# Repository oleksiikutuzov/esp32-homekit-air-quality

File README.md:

# ESP32 HomeKit Air Quality Sensor
Native Apple HomeKit via ESP32 for the IKEA VINDRIKTNING PM2.5 Air Quality sensor + MH-Z19B CO2 Sensor

The modification doesn't interfere with the VINDRIKTNING device itself. It just reads out data and passes it to HomeKit using ESP32.

This Firmware is a Frankenstein Monster built of some other IKEA VINDRIKTNING projects from kasik96, Hypfer and ESP32 HomeKit implementation from HomeSpan.

_As usual, don't expect any warranties. I am just a hobbyist, not a professional. It works for me, but you take your own risk using it. I am not liable for any damage to your devices._

I also added the MH-Z19B CO2 Sensor, which fits into the second enclosure along with a custom PCB, which can be glued (taped) on top of the VINDRIKTNING device. It follows the existing design and should look nice (I hope). It also has an LED to show the current CO2 level.

## Prerequisites

- ESP-32-WROOM with project PCB
- MH-Z19B CO2 sensor
- 1 NeoPixel LED
- Some short cables
- A soldering iron
- A long PH0 Screwdriver
- Some more components (check the [BOM](https://github.com/oleksiikutuzov/esp32-homekit-air-quality/blob/main/hardware/BOM.txt))

Everything we need from the IKEA sensor is accessible via easy-to-solder test points or microcontroller pins.

## Hardware
### VINDRIKTNING

To reach the original PCB from IKEA, we need to unscrew the four visible screws in the back of the enclosure.

As you can see in this image, you'll need to solder wires to GND (black), 5V (red), and the Testpoint that is connected to the TX of the
Particle Sensor (lighter green). Additionally, you need to solder the cable to one of the pins of the microcontroller (darker green) to be able to read the values from the built-in light sensor. On my PCB I am using a JST-GH (1.25 mm) connector to connect all the wires from VINDRIKTNING. Make sure the cables from IKEA PCB have enough cross-section to carry the current because generic Chinese JST-GH connectors' cables are too thin.

Solder the custom PCB, install the MH-Z19B CO2 sensor, connect the VINDRIKTNING board and NeoPixel LED via JST connectors and you are done.

### Sensor
The PCB has pads for 1.25 mm keyless 3-pin and 4-pin JST connectors, the lid has 4 mm holes for M3 threaded inserts and holes for small screws to fix the plate on which NeoPixel is mounted.

## Software

Here you can see, which pins are used and pre-defined in the firmware:
```c++
*               ╔═════════════════════════════╗
*               ║┌─┬─┐  ┌──┐  ┌─┐             ║
*               ║│ | └──┘  └──┘ |             ║
*               ║│ |            |             ║
*               ╠═════════════════════════════╣
*           +++ ║GND                       GND║ +++
*           +++ ║3.3V                     IO23║ USED_FOR_NOTHING
*               ║                         IO22║
*               ║IO36                      IO1║ TX
*               ║IO39                      IO3║ RX
*               ║IO34                     IO21║
*               ║IO35                         ║ NC
*               ║IO32                     IO19║ MHZ TX
*               ║IO33                     IO18║ MHZ RX
*  LIGHT_SENSOR ║IO25                      IO5║
*       LED_RED ║IO26                     IO17║
*               ║IO27                     IO16║ NEOPIXEL
*  VINDRIKTNING ║IO14                      IO4║
*               ║IO12                      IO0║ BUTTONS
*               ╚═════════════════════════════╝
```

The firmware can be built and flashed using the Arduino IDE.

For this, you will need to add ESP32 support to it.

Furthermore, you will also need to install the following libraries using the Library Manager:

* Adafruit NeoPixel
* HomeSpan
* EspSoftwareSerial

And some libraries manually:

1. Go to this GitHub repo and download it as a ZIP - [AsyncElegantOTA](https://github.com/ayushsharma82/AsyncElegantOTA)
2. In Arduino IDE select "Sketch" -> "Include Library" and "Add .ZIP Library..." and select downloaded ZIP
3. Do previous steps to the following libraries:
   * [ESPAsyncWebServer](https://github.com/me-no-dev/ESPAsyncWebServer)
   * [AsyncTCP](https://github.com/me-no-dev/AsyncTCP)
   * [ErriezMHZ19B](https://github.com/Erriez/ErriezMHZ19B)
4. Download and open this repository in Arduino IDE (or VSCode with Arduino extension)
5. Set the upload speed to 115200
6. Build, flash, and you're done

Instead of Arduino IDE OTA, the web server update was implemented. You can flash binary at `http://[DEVICE IP]/update`.
There is a reboot link. Opening `http://[DEVICE IP]/reboot` will force the device to reboot.

The device can also be controlled by the button on the backside. More on [HomeSpan docs](https://github.com/HomeSpan/HomeSpan/blob/master/docs/UserGuide.md)

A list of settings variables is in the sketch. You can adjust the values up to your needs.

## Connect to HomeKit

1. Plug your Air Quality sensor to power (ESP32 is powered through VINDRIKTNING).
2. Press the button on the backside until the LED starts blinking rapidly and release it. Now it is in the configuration mode (More on [HomeSpan docs](https://github.com/HomeSpan/HomeSpan/blob/master/docs/UserGuide.md)). Press it two more times until the LED starts blinking 3 times in a row. This means mode 3 is chosen. Hold the button for 3-4 seconds once again and the WiFi AP will be started.
3. Go to WiFi settings on your iPhone/iPad and connect to the "HomeSpan-Setup" WiFi network, password `homespan`.
4. You will choose your WiFi network and set the setup code for the accessory.
5. Go to your Home app and select "Add Accessory"
6. Select "More Options" and you should see your Air Quality Sensor there.

## Prometheus metrics

The firmware creates a simple HTTP server to share the metrics to the Prometheus host server. The update interval is 10 seconds, the same as for the HomeKit data. Is available at the `http://DEVICE_IP/metrics` default port is `80`.

Installation guides for Raspberry Pi 4: [Grafana](https://pimylifeup.com/raspberry-pi-grafana/), [Prometheus](https://pimylifeup.com/raspberry-pi-prometheus/).

To add metrics to your Prometheus config:

1. Stop the Prometheus service:
```
sudo systemctl stop prometheus
```
2. Edit your config:
```
nano /home/pi/prometheus/prometheus.yml
```
Paste the following to the end of the config (Keep in mind indentation):
```
- job_name: "air_sensor"
    scrape_interval: 30s
    honor_labels: true
    static_configs:
    - targets: ['DEVICE_IP:80']
```
*Scrape interval determines, how often the server will check the device for metrics updates*

3. Start the Prometheus service again:
```
sudo systemctl start prometheus
```

## References and sources

- @kasik96 for HomeKit ESP8266 VINDRIKTNING custom firmware [GitHub link](https://github.com/kasik96/esp8266-vindriktning-particle-sensor-homekit)
- @Hypfer for MQTT ESP8266 VINDRIKTNING custom firmware [GitHub link](https://github.com/Hypfer/esp8266-vindriktning-particle-sensor)
- @HomeSpan for ESP32 HomeKit firmware [GitHub link](https://github.com/HomeSpan/HomeSpan)
- @Erriez for MH-Z19B CO2 sensor library [GitHub link](https://github.com/Erriez/ErriezMHZ19B)
- [@haxfleisch](https://twitter.com/haxfleisch) for their teardown of the device.

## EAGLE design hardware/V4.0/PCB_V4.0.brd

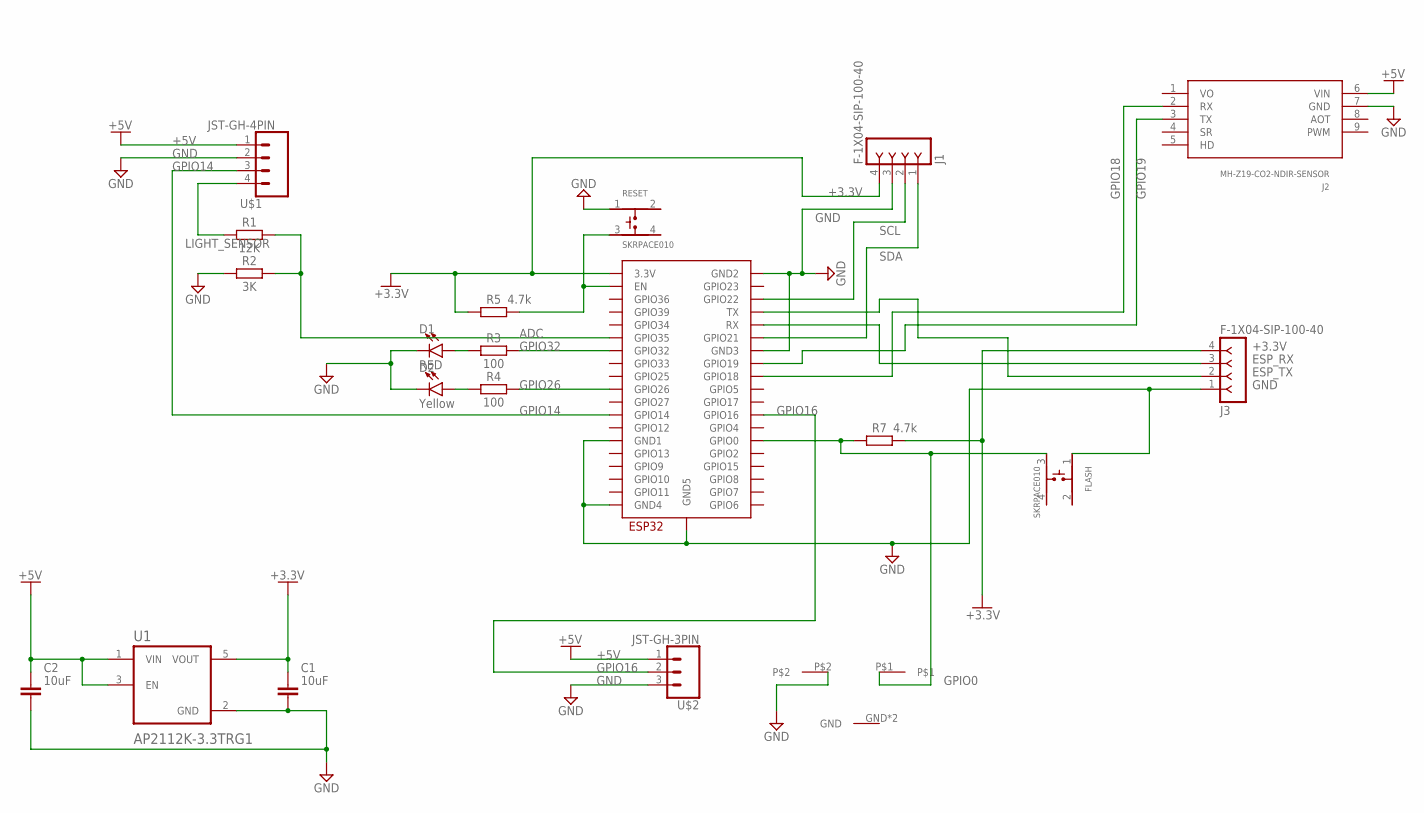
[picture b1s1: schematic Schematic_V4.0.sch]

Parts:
C1, C2: 10uF; CAPC1608X85
D1: RED; LED-0603
D2: Yellow; LED-0603
FLASH: SKRPACE010; SW_SKRPACE010
J1, J3: F-1X04-SIP-100-40; SIP-100-04-40
J2: MH-Z19-CO2-NDIR-SENSOR; MH-Z19
R1: 12K; RESC1608X60
R2: 3K; RESC1608X60
R3, R4: 100; RESC1608X60
R5, R7: 4.7k; RESC1608X60
RESET: SKRPACE010; SW_SKRPACE010
U1: AP2112K-3.3TRG1; SOT95P285X140-5N
U$1: JST-GH-4PIN
U$2: JST-GH-3PIN
U$3: ESP32-WROOM
U$4: MOMENTARY-SWITCH; SWITCH-MOMENTARY

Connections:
+3.3V: C1.1, J1.4, J3.4, R5.1, R7.2, U1.5 (VOUT), U$3.3V3 (3.3V)
+5V: C2.1, J2.6 (VIN), U1.1 (VIN), U1.3 (EN), U$1.1, U$2.1
ADC: R1.2, R2.2, U$3.IO35 (GPIO35)
ESP_RX: J3.3, U$3.RX
ESP_TX: J3.2, U$3.TX
GND: C1.2, C2.2, D1.C, D2.C, FLASH.1, J1.3, J2.7 (GND), J3.1, R2.1, RESET.1, U1.2 (GND), U$1.2, U$2.3, U$3.GND1, U$3.GND2, U$3.GND3, U$3.GND4, U$3.GND5, U$4.P$2
GPIO0: FLASH.3, R7.1, U$3.IO0 (GPIO0), U$4.P$1
GPIO14: U$1.3, U$3.IO14 (GPIO14)
GPIO16: U$2.2, U$3.IO16 (GPIO16)
GPIO18: J2.2 (RX), U$3.IO18 (GPIO18)
GPIO19: J2.3 (TX), U$3.IO19 (GPIO19)
GPIO26: R4.2, U$3.IO26 (GPIO26)
GPIO32: R3.2, U$3.IO32 (GPIO32)
LIGHT_SENSOR: R1.1, U$1.4
unnamed: D1.A, R3.1
unnamed: D2.A, R4.1
RESET: R5.2, RESET.3, U$3.EN
SCL: J1.2, U$3.IO22 (GPIO22)
SDA: J1.1, U$3.IO21 (GPIO21)
VO: J2.1 (VO)

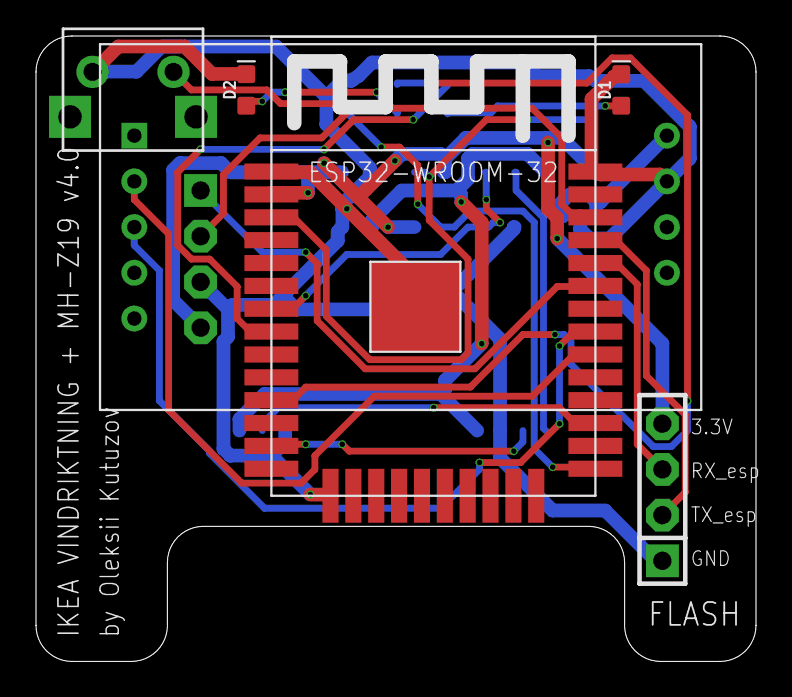
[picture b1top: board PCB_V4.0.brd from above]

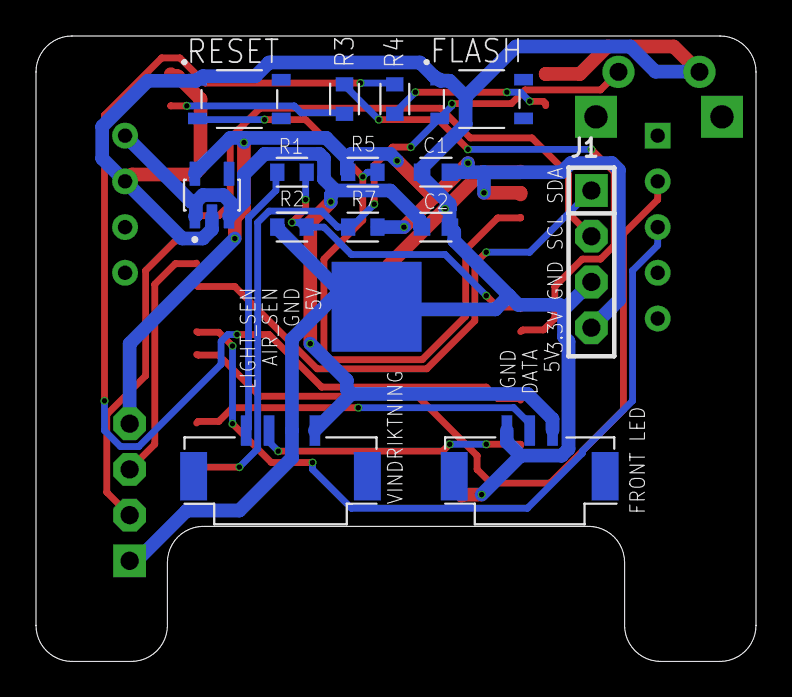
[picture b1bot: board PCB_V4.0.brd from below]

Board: 2 copper layers, 40.0 x 34.7 mm, 20 parts (14 on the bottom side), 19 nets.

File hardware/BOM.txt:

Part  Value                  Device                   Package          Description                                                                 
C1    10uF                   C_CHIP-0603(1608-METRIC) CAPC1608X85      Capacitor - Generic                                                         
C2    10uF                   C_CHIP-0603(1608-METRIC) CAPC1608X85      Capacitor - Generic                                                         
D2    RED                    LED-RED0603              LED-0603         Red SMD LED                                                                 
FLASH SKRPACE010             SKRPACE010               SW_SKRPACE010    Switch Tactile N.O. SPST Button J-Bend 0.05A 16VDC 2.55N SMD Automotive T/R 
J2    MH-Z19-CO2-NDIR-SENSOR MH-Z19-CO2-NDIR-SENSOR   MH-Z19           MH-Z19 - CO2 NDIR SENSOR                                                    
J3    F-1X04-SIP-100-40      F-1X04-SIP-100-40        SIP-100-04-40    FEMALE HEADER                                                               
R1    12K                    R_CHIP-0603(1608-METRIC) RESC1608X60      Resistor Fixed - Generic                                                    
R2    3K                     R_CHIP-0603(1608-METRIC) RESC1608X60      Resistor Fixed - Generic                                                    
R3    100                    R_CHIP-0603(1608-METRIC) RESC1608X60      Resistor Fixed - Generic                                                    
R4    100                    R_CHIP-0603(1608-METRIC) RESC1608X60      Resistor Fixed - Generic                                                    
R5    4.7k                   R_CHIP-0603(1608-METRIC) RESC1608X60      Resistor Fixed - Generic                                                    
R7    4.7k                   R_CHIP-0603(1608-METRIC) RESC1608X60      Resistor Fixed - Generic                                                    
RESET SKRPACE010             SKRPACE010               SW_SKRPACE010    https://a.aliexpress.com/_AWwm9c
U$1   JST-GH-4PIN            JST-GH-4PIN              JST-GH-4PIN      https://a.aliexpress.com/_9IWSRs                                                                           
U$2   JST-GH-3PIN            JST-GH-3PIN              JST-GH-3PIN      https://a.aliexpress.com/_9IWSRs                                                                           
U$3   ESP32-WROOM            ESP32-WROOM              ESP32-WROOM                                                                                 
U$4   MOMENTARY-SWITCH       MOMENTARY-SWITCH         SWITCH-MOMENTARY https://a.aliexpress.com/_AcqTm9 (6x6x6 mm)                                                                            
U1    AP2112K-3.3TRG1        AP2112K-3.3TRG1          SOT95P285X140-5N AP2112 Series 0.6 A 3.3 V Fixed Output SMT LDO Linear Regulator - SOT23-5

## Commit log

2022-02-10 Upload example code
2022-02-10 Adjust characteristics
2022-02-10 Remove comments
2022-02-10 Add support for MH-Z19B
2022-02-10 Move warming up to separate process
2022-02-10 Add initial animation
2022-02-11 Add color change on warm up and according to co2 level
2022-02-11 Add reset peak value
2022-02-11 Add VSCode config
2022-02-11 Add Air quality measurements
2022-02-11 Add autocalibration option
2022-02-11 Add metrics server
2022-02-11 Add uptime and heap metric
2022-02-11 Add brightness control
2022-02-13 Small adjustments to metrics server
2022-02-13 Set auto AP on startup
2022-02-13 Change default vo2 value to 400
2022-02-13 Adjust Accessories names
2022-02-13 Change interval to 10 seconds
2022-02-13 Set default value to exclude metrics during warmup
2022-04-26 Change server, add OTA
2022-04-26 Add timeout for the built in led
2022-05-05 Remove unneeded pin definitions
2022-05-05 Set number of connections to default value
2022-05-06 Set button pin to 0, disable auto AP
2022-05-06 Edit build config
2022-05-06 Remove most of libraries
2022-05-06 Add libraries
2022-05-06 Add more libraries
2022-05-06 Fix sketch name
2022-05-06 Edit libraries
2022-05-06 Add library
2022-05-06 Fix library name
2022-05-06 Add Smoothed library
2022-05-06 Add build parameters
2022-05-06 Change smoothing to library
2022-05-06 Update services
2022-05-06 Remove DEV_Identify.h
2022-05-06 Update config file
2022-05-06 Add hardware files
2022-05-06 Add pictures
2022-05-06 Small fixes
2022-05-07 Update config
2022-05-07 Rename folder
2022-05-07 Add submodules
2022-05-07 Remove submodules
2022-05-07 Remove .gitmodules
2022-05-07 Edit config files
2022-05-17 Small adjustments to config
2022-05-17 Adjust pin scheme
2022-05-17 Update Firmware Revision
2022-05-26 Change header files to .hpp
2022-05-26 Change includes to .hpp
2022-06-08 Update VSCode settings
2022-06-09 Apply some filtering to Air Quality Sensor data
2022-08-02 Change from AsyncWebServer to WebServer and misc
2022-08-02 Update VSCode config
2022-08-09 Minor fixes
2022-08-27 Add temperature and humidity, test brightness
2022-08-30 Add offset to temperature and humidity values
2022-08-30 Reorder hardware, upload new hardware revision
2022-08-30 Apply smoothing to sensor data
2022-08-30 Add sensor values to prometheus metrics
2022-08-30 Warming up condition for metrics, misc adjustments
2022-08-31 Show build time in weblog
2022-08-31 Upload files
2022-08-31 Upload code and binary
2022-08-31 Test Update
2022-08-31 Update files structure and bump another version
2022-08-31 Update links to V4.0 branch
2022-09-04 Switch to PlatformIO
2022-09-04 Edit script
2022-09-04 fix name
2022-09-04 Add libs
2022-12-07 Remove OTA and bins
2022-12-09 Remove modules
2022-12-09 Switch to Arduino IDE
2022-12-12 Use Pixel class of HomeSpan
2022-12-12 Add color fade
2023-01-08 Minor Adjustments

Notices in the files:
parts and their libraries:
con-headers-jp: Copyright (C) 2008, Bob Starr
SparkFun-LED: Licensing: Creative Commons ShareAlike 4.0 International - https://creativecommons.org/licenses/by-sa/4.0
